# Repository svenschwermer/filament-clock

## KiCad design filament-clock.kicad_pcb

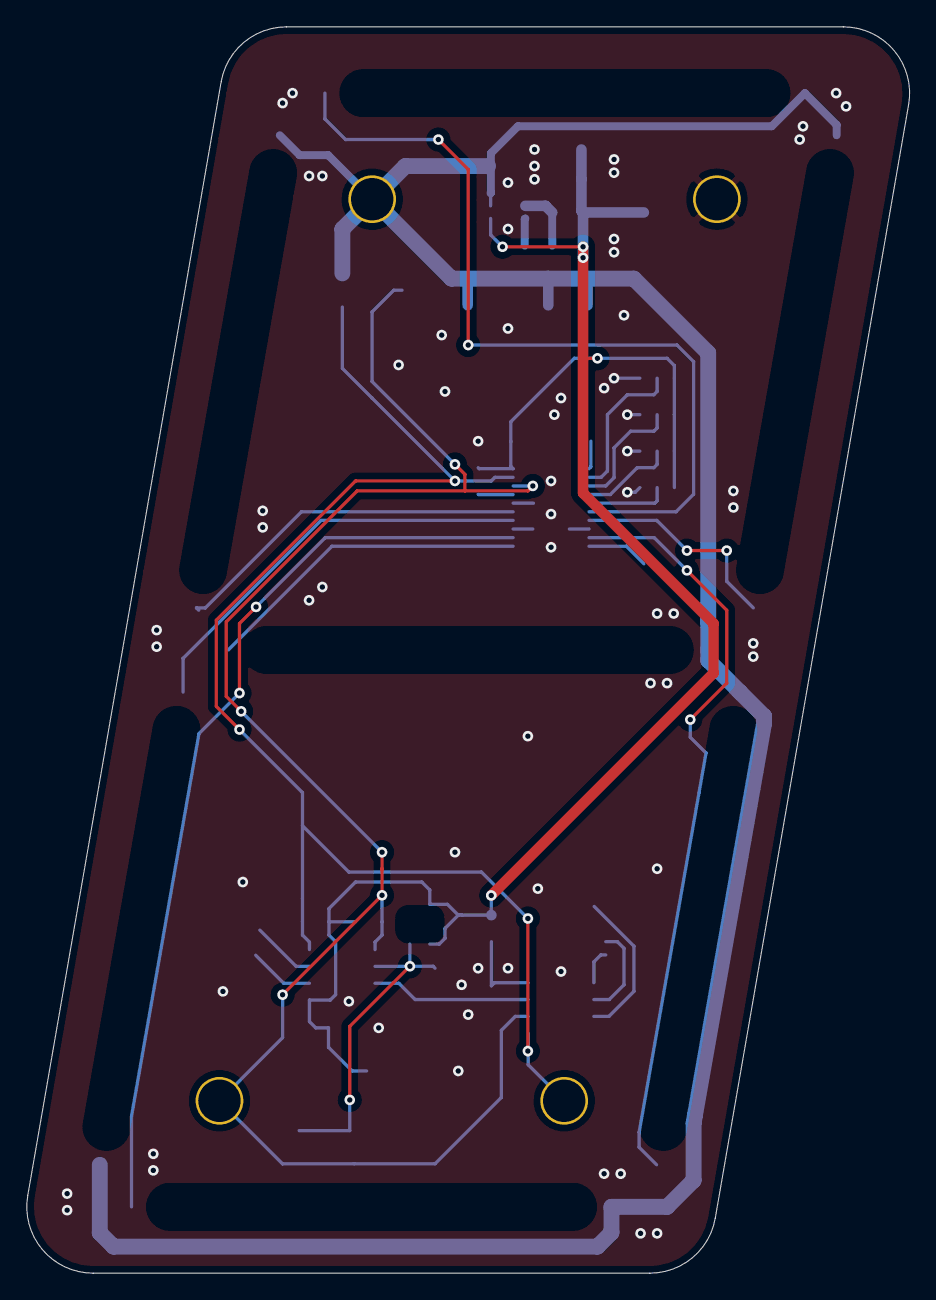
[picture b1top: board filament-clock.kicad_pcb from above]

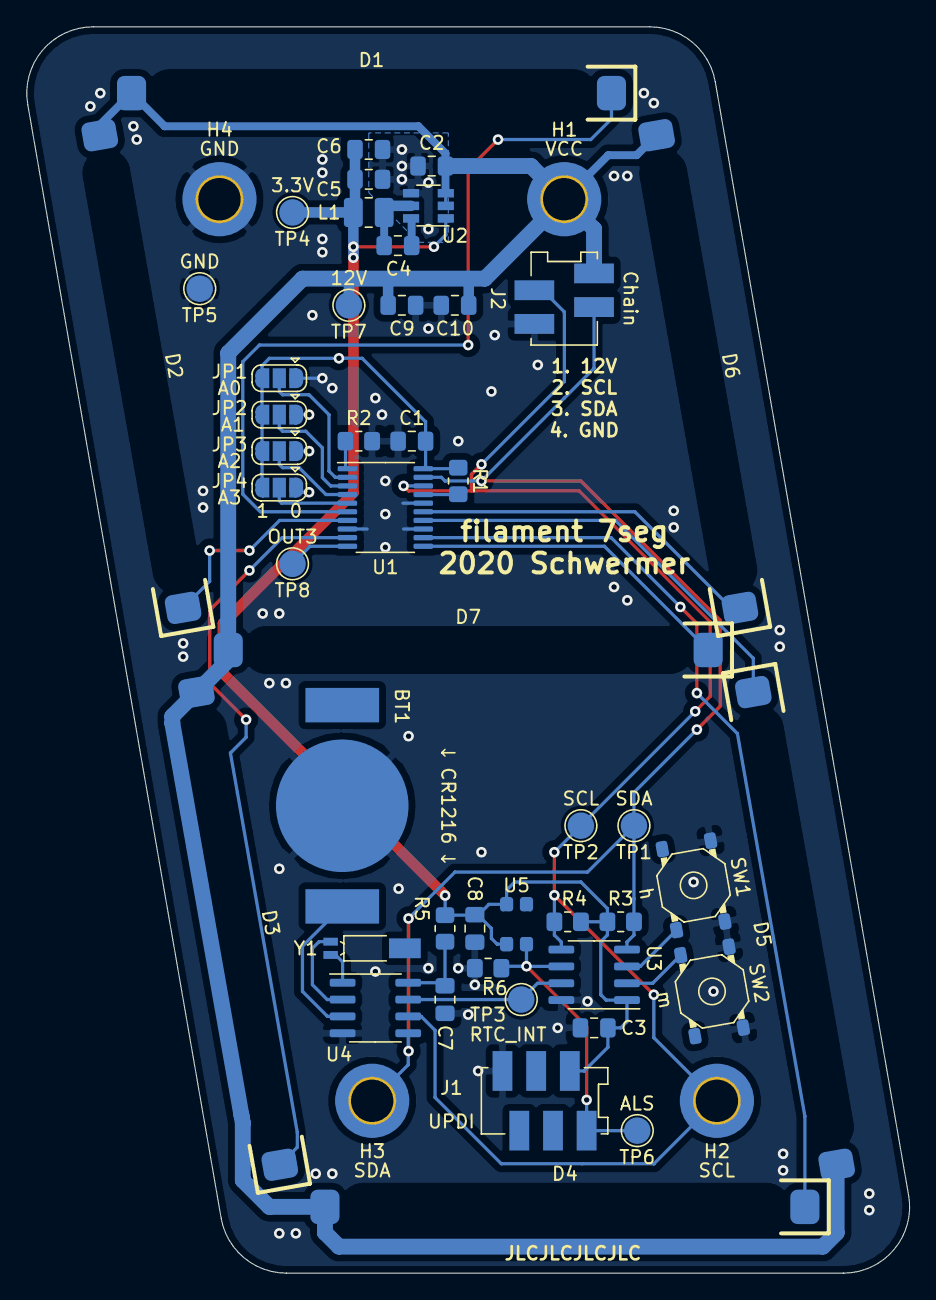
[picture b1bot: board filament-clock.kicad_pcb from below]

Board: 2 copper layers, 66.6 x 94.0 mm, 51 parts (51 on the bottom side), 29 nets.

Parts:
BT1: CR1216; BC-2017
C1, C3, C4, C8: 100n; C_0805_2012Metric_Pad1.18x1.45mm_HandSolder
C2: 10µ; C_0805_2012Metric_Pad1.18x1.45mm_HandSolder
C5, C6: 22µ; C_0805_2012Metric_Pad1.18x1.45mm_HandSolder
C7: 3.3µ; C_0805_2012Metric_Pad1.18x1.45mm_HandSolder
C9, C10: C; C_0805_2012Metric_Pad1.18x1.45mm_HandSolder
D1, D2, D3, D4, D5, D6, D7: LED; filament-led
H1: VCC; MountingHole_3.2mm_M3_DIN965_Pad_TopOnly
H2: SCL; MountingHole_3.2mm_M3_DIN965_Pad_TopOnly
H3: SDA; MountingHole_3.2mm_M3_DIN965_Pad_TopOnly
H4: GND; MountingHole_3.2mm_M3_DIN965_Pad_TopOnly
J1: UPDI; ConnectorMicromatch-6
J2: Chain; ConnectorMicromatch-4
JP1: A0; SolderJumper-3_P1.3mm_Open_RoundedPad1.0x1.5mm
JP2: A1; SolderJumper-3_P1.3mm_Open_RoundedPad1.0x1.5mm
JP3: A2; SolderJumper-3_P1.3mm_Open_RoundedPad1.0x1.5mm
JP4: A3; SolderJumper-3_P1.3mm_Open_RoundedPad1.0x1.5mm
L1: 4.7µ; L_1008_2520Metric_Pad1.43x2.20mm_HandSolder
R1: 10k; R_0805_2012Metric_Pad1.20x1.40mm_HandSolder
R2: 3.9k; R_0805_2012Metric_Pad1.20x1.40mm_HandSolder
R3, R4: 4.7k; R_0805_2012Metric_Pad1.20x1.40mm_HandSolder
R5: 1k; R_0805_2012Metric_Pad1.20x1.40mm_HandSolder
R6: 5k; R_0805_2012Metric_Pad1.20x1.40mm_HandSolder
SW1: h; pts526
SW2: m; pts526
TP1: SDA; TestPoint_Pad_D2.0mm
TP2: SCL; TestPoint_Pad_D2.0mm
TP3: RTC_INT; TestPoint_Pad_D2.0mm
TP4: 3.3V; TestPoint_Pad_D2.0mm
TP5: GND; TestPoint_Pad_D2.0mm
TP6: ALS; TestPoint_Pad_D2.0mm
TP7: 12V; TestPoint_Pad_D2.0mm
TP8: OUT3; TestPoint_Pad_D2.0mm
U1: TLC59108xPW; TSSOP-20_4.4x6.5mm_P0.65mm
U2: AP63203WU; TSOT-23-6
U3: ATtiny412-SS; SOIC-8_3.9x4.9mm_P1.27mm
U4: PCF8523T; SOIC-8_3.9x4.9mm_P1.27mm
U5: apds-9006; chipled-4
Y1: 32.768kHz; Crystal_SMD_MicroCrystal_MS3V-T1R

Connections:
+3V3: C1.1, C3.2, C5.1, C6.1, C8.1, J1.2, JP1.3, JP2.3, JP3.3, JP4.3, L1.2, R1.1, R3.1, R4.1, R5.1, TP4.1, U1.20, U2.1, U3.1, U5.2, U5.3
+12V: C2.1, C9.1, C10.1, D1.2, D2.2, D3.2, D4.2, D5.2, D6.2, D7.2, H1.1, J2.1, TP7.1, U2.2, U2.3
GND: BT1.2, C1.2, C2.2, C3.1, C5.2, C6.2, C7.1, C8.2, C9.2, C10.2, H4.1, J1.6, J2.4, JP1.1, JP2.1, JP3.1, JP4.1, R2.2, R6.2, SW1.3, SW1.4, SW2.3, SW2.4, TP5.1, U1.8, U1.13, U1.16, U2.4, U3.8, U4.4
unnamed: BT1.1, U4.3
unnamed: C4.1, L1.1, U2.5
unnamed: C4.2, U2.6
unnamed: C7.2, R5.2, U4.8
unnamed: D1.1, U1.6
unnamed: D2.1, U1.7
unnamed: D3.1, U1.9
unnamed: D4.1, U1.12
unnamed: D5.1, U1.14
unnamed: D6.1, U1.15
unnamed: D7.1, U1.11
unnamed: J1.1, R6.1, TP6.1, U3.6, U5.1
unnamed: JP1.2, U1.2
unnamed: JP2.2, U1.3
unnamed: JP3.2, U1.4
unnamed: JP4.2, U1.5
unnamed: R1.2, U1.17
unnamed: R2.1, U1.1
unnamed: SW1.1, U3.3
unnamed: SW2.2, U3.2
unnamed: TP8.1, U1.10
unnamed: U4.1, Y1.1
unnamed: U4.2, Y1.2
RTC_INT: TP3.1, U3.7, U4.7
SCL: H2.1, J2.2, R4.2, TP2.1, U1.18, U3.5, U4.6
SDA: H3.1, J2.3, R3.2, TP1.1, U1.19, U3.4, U4.5

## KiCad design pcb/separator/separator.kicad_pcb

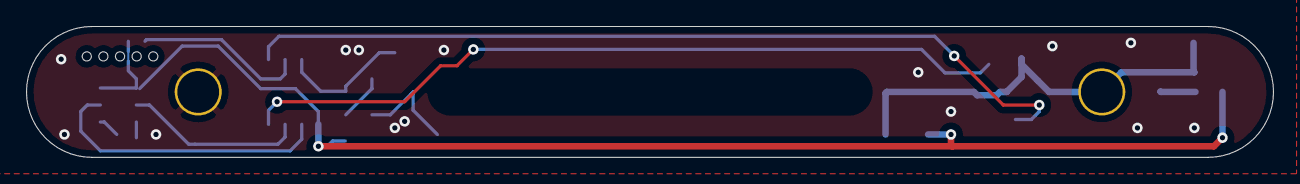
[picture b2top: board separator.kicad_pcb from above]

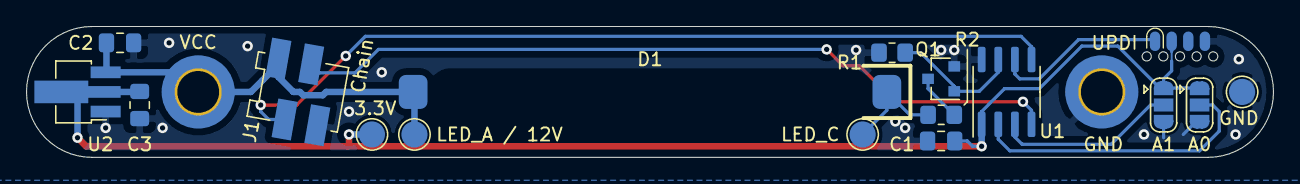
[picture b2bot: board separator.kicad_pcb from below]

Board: 2 copper layers, 95.3 x 10.0 mm, 19 parts (19 on the bottom side), 11 nets.

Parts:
C1: 100n; C_0805_2012Metric_Pad1.18x1.45mm_HandSolder
C2, C3: 10µ; C_0805_2012Metric_Pad1.18x1.45mm_HandSolder
D1: LED; filament-led
H1: VCC; MountingHole_3.2mm_M3_DIN965_Pad_TopOnly
H2: GND; MountingHole_3.2mm_M3_DIN965_Pad_TopOnly
J1: Chain; ConnectorMicromatch-4
J2: UPDI; SOIC_clipProgSmall_onesided
JP1: A0; SolderJumper-3_P1.3mm_Open_RoundedPad1.0x1.5mm
JP2: A1; SolderJumper-3_P1.3mm_Open_RoundedPad1.0x1.5mm
Q1: 2N7002; SOT-23
R1: 10k; R_0805_2012Metric_Pad1.20x1.40mm_HandSolder
R2: 301; R_0805_2012Metric_Pad1.20x1.40mm_HandSolder
TP1: LED_A / 12V; TestPoint_Pad_D2.0mm
TP2: LED_C; TestPoint_Pad_D2.0mm
TP4: GND; TestPoint_Pad_D2.0mm
TP5: 3.3V; TestPoint_Pad_D2.0mm
U1: ATtiny412-SS; SOIC-8_3.9x4.9mm_P1.27mm
U2: AZ1117-3.3; SOT-89-3_Handsoldering

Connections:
+3V3: C1.2, C3.1, J2.2, JP1.1, JP2.1, TP5.1, U1.1, U2.2
+12V: C2.1, D1.2, H1.1, J1.1, TP1.1, U2.3
A0: JP1.2, U1.2
A1: JP2.2, U1.3
GND: C1.1, C2.2, C3.2, H2.1, J1.4, J2.4, JP1.3, JP2.3, Q1.2, R1.1, TP4.1, U1.8, U2.1
unnamed: D1.1, R2.1, TP2.1
unnamed: Q1.1, R1.2, U1.7
unnamed: Q1.3, R2.2
SCL: J1.2, U1.5
SDA: J1.3, U1.4
UPDI: J2.1, U1.6

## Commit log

2020-12-10 PCB Rev 1
2020-12-13 Fix PCB
2020-12-13 Add firmware
    We can talk to the LED driver and read the seconds register from the
    RTC. This all works so far.
2020-12-13 Add i2cdriver test script
2020-12-13 Move kicad files into pcb folder
2020-12-13 Tidy up 3D models
2020-12-13 Add SOICbite footprints
2020-12-18 Fix wrong filename of ALS 3D model
2020-12-18 Fixup PCB
2020-12-18 Add separator PCB
    Dimensions should be correct.
2021-02-21 fw: Not working parts resolved
2021-02-21 Segment firmware complete
2021-02-21 fw: Some parts working
    Problems:
    1. 2nd digit doesn't work when RTC is read
    2. Separator doesn't blink
2021-02-21 Restructure repo
2021-02-21 fw: Separate object file directory
2021-02-21 fw: RTC second interrupt
2021-02-21 Add script to set RTC time
2021-06-27 Complete 6-digit firmware
